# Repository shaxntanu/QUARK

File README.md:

<div align="center">

# QUARK

**A tiny desk display for Codex usage and live Windows telemetry.**

ESP32-C3 · 128×64 OLED · USB serial · Windows companion

</div>

QUARK pairs an ESP32-C3 SuperMini with a monochrome OLED. A lightweight Windows companion reads local PC metrics and Codex App Server usage, then sends them to the device over USB. A physical switch selects Codex or system pages; a button advances pages or requests a refresh.

## At a glance

- **Codex:** today's and lifetime tokens, seven-day token trend, five-hour and weekly allowance, usage streaks, and longest running turn.
- **PC:** CPU load and frequency, memory use and free memory, NVIDIA GPU load/temperature/VRAM, system-drive use/free space, network throughput, uptime, battery state when available, and a ChatGPT HTTPS reachability check.
- **OLED:** one clear metric or a pair of related readings per page, with line charts for changing values.
- **Connection:** USB reconnects automatically. A brief connection chime plays once after the selected feed is stable; temporary Codex errors keep the last readings visible until they age out.
- **Status LEDs:** blue for a healthy selected feed, red for offline/error, and red plus blue while connecting or refreshing. The faulty green channel is unused.

## Project status

The repository contains a Windows companion, ESP32-C3 firmware, KiCad source, and fabrication exports. The companion and firmware source identify themselves as version 1.2.0; the latest published GitHub release is `v1.1.0`. This audit rebuilt the software and checked the CAD files, but did not perform a new hardware-in-the-loop session.

The project is an engineering prototype and personal telemetry utility. It does not claim research novelty or measured performance results. No `LICENSE` file is present, so reuse and redistribution terms have not been specified.

## Engineering docs

- [Architecture and interfaces](docs/architecture.md)
- [Requirements and scope](docs/requirements.md)
- [Data collection methodology](docs/methodology.md)
- [Hardware integration](docs/hardware.md)
- [Verification evidence](docs/verification.md)
- [Traceability matrix](docs/traceability.md)
- [Security notes](docs/security.md)
- [Limitations](docs/limitations.md) and [roadmap proposals](docs/roadmap.md)
- [Compatibility matrix](docs/compatibility.md)
- [Failure analysis](docs/failure-analysis.md) and [assumptions](docs/assumptions.md)
- [Hardware references](docs/hardware-references.md)
- [Research sources](docs/research-sources.md)
- [Engineering evidence](docs/engineering-evidence.md)
- [Generated artifact provenance](docs/generated-artifacts.md)
- [AI change audit](docs/AI_CHANGE_AUDIT.md) and [skills registry](docs/AI_SKILLS_REFERENCE.md)
- [Decision records](docs/decisions/)
- [Dependency inventory](docs/sbom.md)
- [KiCad workflow research notes](docs/research-notes.md)
- [Repository audit summary](docs/audit.md)
- [Verification script](scripts/verify.ps1) and [documentation checker](scripts/check_docs.py)

The HTTPS indicator only checks whether the computer can open a TCP connection to `chatgpt.com` on port 443. It helps distinguish a general network problem from a Codex App Server problem; it does not prove that Codex authentication or usage requests are working.

## OLED pages

### Codex mode

1. Tokens today, with lifetime tokens in the footer.
2. Seven-day token trend, normalized to the busiest day in that period, with the peak count.
3. Five-hour allowance remaining and its reset estimate.
4. Weekly allowance remaining and its reset estimate.
5. Current and longest usage streak.
6. Longest running Codex turn.

### System mode

1. CPU load and current frequency.
2. Memory used and available memory.
3. GPU load and temperature.
4. GPU memory use.
5. System-drive use and free space.
6. Download and upload rates with separate trend charts.
7. ChatGPT HTTPS reachability, system uptime, and battery state when available.

NVIDIA GPU readings require `nvidia-smi`; they show `--` when that tool or a supported GPU is unavailable. CPU temperature is not reported because Windows' standard psutil interface does not provide it reliably.

## Hardware

The carrier PCB is designed for an **ESP32-C3 SuperMini 2×8** module and an SH1106 128×64 OLED.

| Part | ESP32-C3 GPIO |
|---|---:|
| OLED SDA | 0 |
| OLED SCL | 1 |
| Page/refresh button | 3 |
| Status LED red | 4 |
| Passive piezo buzzer | 5 |
| Codex/System switch | 6 |
| Status LED blue | 10 |

The button and switch use `INPUT_PULLUP` and should connect to GND when closed. Use current-limiting resistors for the red and blue LED channels. GPIO 7's faulty green channel is not used.

The KiCad schematic, PCB, BOM, previews, Gerbers, and drill files are in [`hardware/QUARK_SuperMini_Carrier`](hardware/QUARK_SuperMini_Carrier/README.md).

## Install the Windows companion

Build the standalone executable with Python 3.12:

```powershell
.\scripts\build_exe.ps1
```

Install it, add it to the current Windows user's Startup folder, and launch it:

```powershell
.\scripts\install_startup.ps1
```

The companion detects the QUARK serial device, reconnects after unplug/replug, and keeps PC telemetry running while Codex data is unavailable. Rotating diagnostic logs are stored in `%LOCALAPPDATA%\QUARK\quark.log`.

To remove the startup shortcut:

```powershell
.\scripts\remove_startup.ps1
```

Codex pages require the Codex CLI to be installed and signed in for the same Windows user. PC pages work independently. For diagnostics, run `py -3.12 .\quark.py --self-test`; list serial ports with `py -3.12 .\quark.py --list-ports`.

## Flash the firmware

1. Install the Arduino ESP32 core 3.x and the U8g2 library.
2. Open `QUARK.ino` in Arduino IDE and select an ESP32-C3 board.
3. Enable **USB CDC On Boot**.
4. Upload the sketch and close Serial Monitor before the companion connects.

The sketch uses `U8G2_SH1106_128X64_NONAME_F_HW_I2C`. Change the constructor if your OLED uses another controller. The companion does not flash the board.

## USB serial protocol

Messages are newline-terminated ASCII at 115200 baud. Values unavailable on the current computer are sent as `--`.

```text
AI|TODAY=18.4K|LIFE=1.42M|H5=74|WEEK=61|H5R=2h14m|WR=3d4h|PEAK=4.2K|STREAK=3|BEST=12|LONGEST=2h14m|D7=0,10,38,22,100,56,64
SYS|CPU=42|GPU=68|RAM=57|TEMP=71|VRAM=36|DISK=62|FREE=14.2G|DFREE=215G|DN=1.2M|UP=84K|DNP=24|UPP=3|FREQ=3.6G|SYSUP=3d4h|BAT=87|AC=ON|WEB=OK
```

The ESP32 answers `PING` with `PONG` for device discovery. It also accepts `MODE|AI`, `MODE|SYS`, `REFRESH|AI`, and `REFRESH|SYS`.

## Build firmware from the command line

With Arduino CLI and the required ESP32 core and U8g2 library installed:

```powershell
arduino-cli compile --fqbn esp32:esp32:esp32c3:CDCOnBoot=cdc .
```

## Development

Run the canonical Windows verification workflow with Python 3.12:

```powershell
py -3.12 -m pip install -r requirements.txt -r requirements-build.txt
.\scripts\verify.ps1
```

To include a local ESP32-C3 firmware compile, install Arduino CLI, the ESP32 core and U8g2, then run `.scriptserify.ps1 -IncludeFirmware`. KiCad ERC/DRC checks use the commands in the hardware README and are not part of the default script.

See [CONTRIBUTING.md](CONTRIBUTING.md) for the repeatable build and review workflow, and [SECURITY.md](SECURITY.md) for vulnerability reporting. Citations for version 1.2.0 are described in [CITATION.cff](CITATION.cff). The project has no declared license yet.

## Repository layout

```text
QUARK.ino                         ESP32-C3 firmware and OLED UI
quark.py                          Windows telemetry/Codex companion
tests/test_quark.py               Python unit and protocol regression tests
scripts/                          Windows packaging and startup scripts
hardware/QUARK_SuperMini_Carrier/ KiCad design, BOM, and fabrication files
docs/                             Architecture, verification, security, and audit docs
.github/                          CI and dependency update configuration
```

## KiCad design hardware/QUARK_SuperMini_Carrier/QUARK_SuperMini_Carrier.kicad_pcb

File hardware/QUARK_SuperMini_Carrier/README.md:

# QUARK ESP32-C3 SuperMini Carrier

KiCad source for a two-layer carrier board that connects QUARK's ESP32-C3 SuperMini, OLED, mode switch, page button, passive piezo, and red/blue status LEDs.

## Design files

- `QUARK_SuperMini_Carrier.kicad_pro`: KiCad project.
- `QUARK_SuperMini_Carrier.kicad_sch`: schematic.
- `QUARK_SuperMini_Carrier.kicad_pcb`: routed PCB.
- `QUARK.kicad_sym`, `QUARK.pretty/`, and the library tables: project-local symbol and footprint libraries.
- `BOM.csv`: board and off-board parts.
- `firmware/QUARK_ESP32-C3_SuperMini_CDC.bin`: merged 4 MB ESP32-C3 flash image with USB CDC on boot enabled.
- `fabrication/`: Gerbers, Excellon drill files, and drill maps.
- `preview/`: schematic and board preview images.
- `scripts/generate_schematic.py` and `scripts/generate_board.py`: source generators.

## Board and module fit

The carrier outline is 70.104 × 55.372 mm, 1.6 mm thick, with four 3.2 mm non-plated M3 holes. The module footprint is for an ESP32-C3 SuperMini with two 8-pin rows on 2.54 mm pitch and 15.24 mm between row centers. Fit two 1×8 female socket strips to the carrier, then plug the module in with its USB-C connector toward the board's top edge. The nominal module outline is 22.52 × 18 mm per the [module datasheet](https://dl.artronshop.co.th/ESP32-C3%20SuperMini%20datasheet.pdf); SuperMini clones vary, so compare the module and header spacing before ordering a batch.

## Connectors and assembly

All board connectors use 2.54 mm pitch. Connector pin 1 is identified on the silkscreen.

| Ref. | Pin order | Connection |
|---|---|---|
| J1 | GND, 3V3, SCL, SDA | External 128×64 OLED; SCL is GPIO1 and SDA is GPIO0. |
| J2 | AI, COM, SYS OPEN | SPDT mode switch: connect COM to AI/GND for AI mode; leave COM open for System mode (`INPUT_PULLUP`). |
| J3 | GPIO5, GND | Passive piezo disc only; plays startup/control tones and the new-connection acknowledgement. |
| SW1 | N/A | Page/refresh button from GPIO3 to GND. |
| D1, D2 | N/A | Red and blue active-high status LEDs, each with a 330 Ω series resistor. |

The OLED module and mode switch are off-board. J1–J3 are plated header footprints; install pin headers or solder leads as needed. Do not connect a high-current magnetic buzzer directly to GPIO5. The ESP32-C3 SuperMini provides the USB interface and board-level power regulation.

## Fabrication

The `fabrication/` folder contains copper, solder-mask, silkscreen, paste, and outline Gerbers, plus separate PTH and NPTH Excellon files and drill maps. Upload [`QUARK_SuperMini_Carrier_gerbers.zip`](fabrication/QUARK_SuperMini_Carrier_gerbers.zip) to the board fabricator, or upload the individual Gerber and drill files. The board uses two copper layers and a 1.6 mm FR-4 stackup.

## Validation

The checked-in design was checked with KiCad CLI 10.0.7. The 2026-11-02 reports contain zero included ERC/DRC violations, zero unconnected items, and zero schematic-parity issues. They also have 4 ERC checks and 7 DRC checks explicitly ignored; see [`docs/verification.md`](../../docs/verification.md) for the exact list. Zero included violations is not a complete manufacturing or assembly certification. Re-run checks after edits with KiCad 10:

```powershell
kicad-cli sch erc QUARK_SuperMini_Carrier.kicad_sch
kicad-cli pcb drc --schematic-parity --refill-zones QUARK_SuperMini_Carrier.kicad_pcb
```

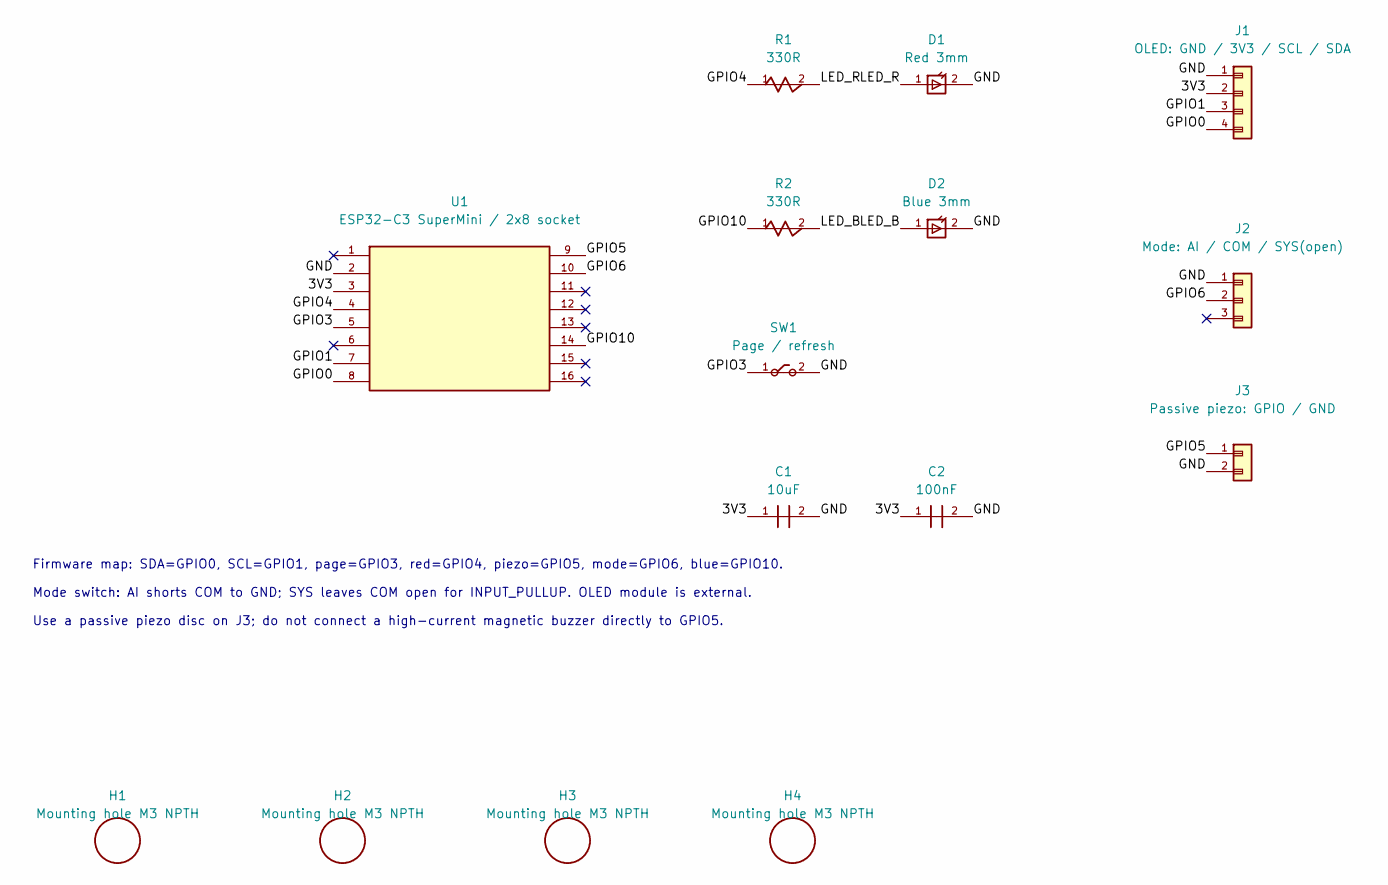
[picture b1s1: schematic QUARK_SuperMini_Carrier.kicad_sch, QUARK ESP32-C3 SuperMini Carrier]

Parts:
C1: 10uF; C_Disc_D5.0mm_W2.5mm_P5.00mm
C2: 100nF; C_Disc_D5.0mm_W2.5mm_P5.00mm
D1: Red 3mm; LED_D3.0mm
D2: Blue 3mm; LED_D3.0mm
H1, H2, H3, H4: Mounting hole M3 NPTH; MountingHole_3.2mm_M3
J1: OLED: GND / 3V3 / SCL / SDA; PinHeader_1x04_P2.54mm_Vertical
J2: Mode: AI / COM / SYS(open); PinHeader_1x03_P2.54mm_Vertical
J3: Passive piezo: GPIO / GND; PinHeader_1x02_P2.54mm_Vertical
R1, R2: 330R; R_Axial_DIN0204_L3.6mm_D1.6mm_P7.62mm_Horizontal
SW1: Page / refresh; SW_TH_Tactile_Omron_B3F-100x
U1: ESP32-C3 SuperMini / 2x8 socket; ESP32C3_SuperMini_Socket_2x8

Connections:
/3V3: C1.1, C2.1, J1.2, U1.3 (3V3)
/GND: C1.2, C2.2, D1.2 (K), D2.2 (K), J1.1, J2.1, J3.2, SW1.2, U1.2 (GND)
/GPIO0: J1.4, U1.8 (GPIO0)
/GPIO1: J1.3, U1.7 (GPIO1)
/GPIO3: SW1.1, U1.5 (GPIO3)
/GPIO4: R1.1, U1.4 (GPIO4)
/GPIO5: J3.1, U1.9 (GPIO5)
/GPIO6: J2.2, U1.10 (GPIO6)
/GPIO10: R2.1, U1.14 (GPIO10)
/LED_B: D2.1 (A), R2.2
/LED_R: D1.1 (A), R1.2

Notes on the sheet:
Firmware map: SDA=GPIO0, SCL=GPIO1, page=GPIO3, red=GPIO4, piezo=GPIO5, mode=GPIO6, blue=GPIO10.
Mode switch: AI shorts COM to GND; SYS leaves COM open for INPUT_PULLUP. OLED module is external.
Use a passive piezo disc on J3; do not connect a high-current magnetic buzzer directly to GPIO5.

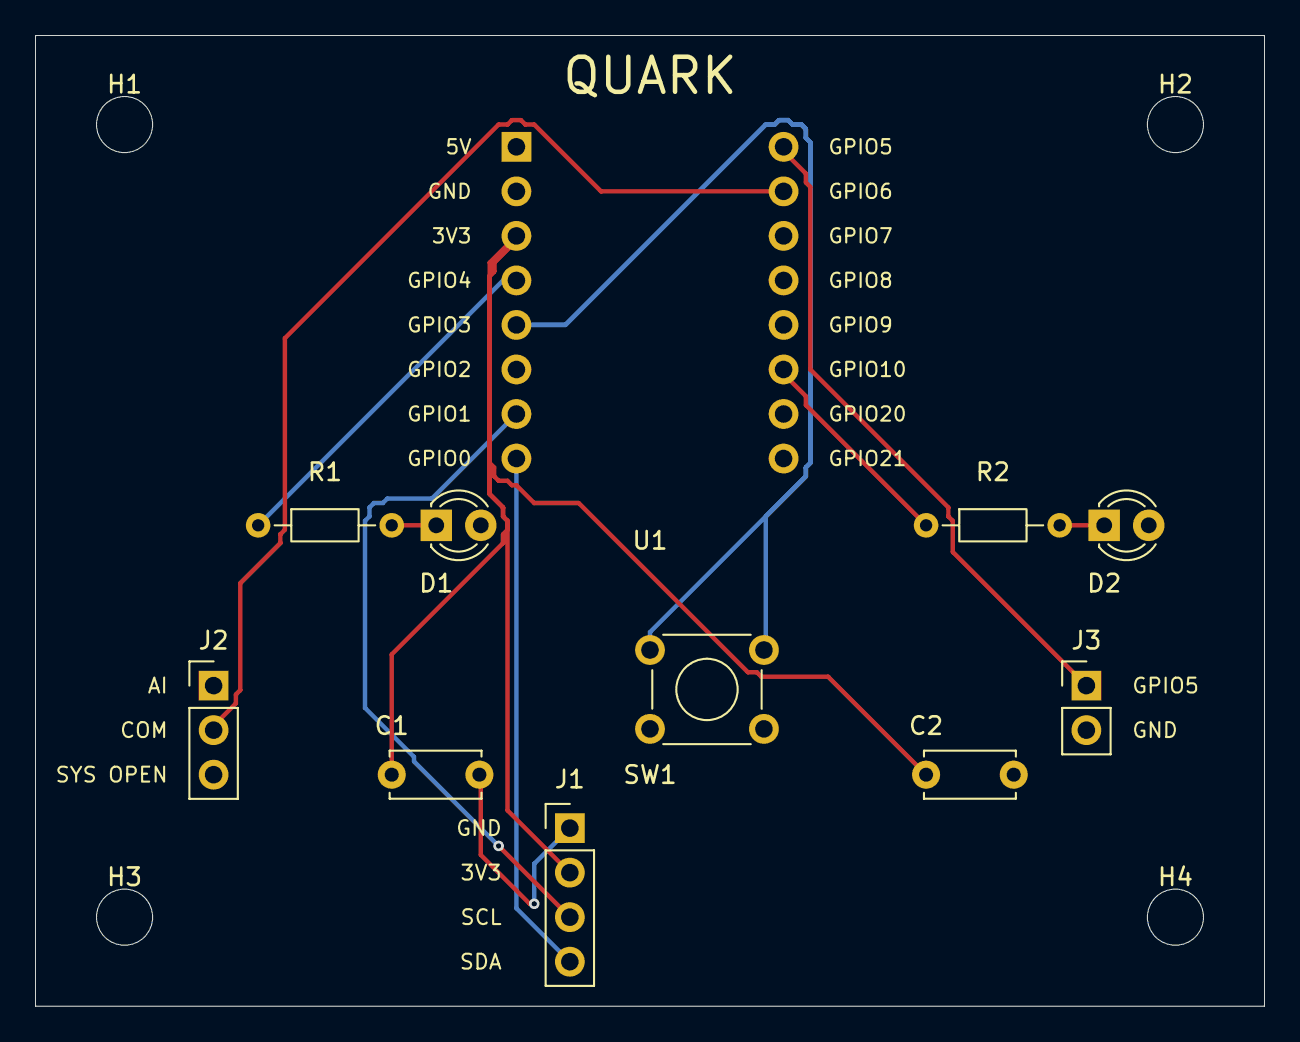
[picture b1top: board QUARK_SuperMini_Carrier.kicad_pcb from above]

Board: 2 copper layers, 70.1 x 55.4 mm, 15 parts (0 on the bottom side), 11 nets.

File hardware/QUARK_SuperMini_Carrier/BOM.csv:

Reference,Quantity,Description,Specification / footprint,Notes
U1,1,ESP32-C3 SuperMini module,2 x 8 pins; 2.54 mm pitch,USB-C faces board top; module not included with bare PCB
U1 socket,2,1 x 8 female socket strip,2.54 mm pitch,Install on carrier; socket rows are 15.24 mm center-to-center
J1,1,1 x 4 straight pin header or wire harness,2.54 mm pitch,External OLED: GND / 3V3 / SCL / SDA
J2,1,1 x 3 straight pin header or wire harness,2.54 mm pitch,External mode switch: AI / COM / SYS open
J3,1,1 x 2 straight pin header or wire harness,2.54 mm pitch,Passive piezo: GPIO5 / GND
R1 R2,2,Resistor,330 ohm; DIN0204 axial THT,LED current limiting
D1,1,Red through-hole LED,3 mm,Status LED
D2,1,Blue through-hole LED,3 mm,Status LED
SW1,1,Momentary tactile switch,Omron B3F-100x compatible footprint,Page / refresh button
C1,1,Ceramic capacitor,10 uF; 5 mm pitch THT,Power decoupling
C2,1,Ceramic capacitor,100 nF; 5 mm pitch THT,Power decoupling
OLED1,1,OLED module,128 x 64; SH1106; 4-wire I2C,Off-board accessory
SW2,1,SPDT mode switch,ON-ON; center common,Off-board accessory; COM to AI/GND or SYS/open
BZ1,1,Passive piezo disc,GPIO-compatible,Off-board accessory; do not use a high-current magnetic buzzer
H1-H4,4,M3 fastener set,3.2 mm clearance,Optional screws and standoffs for mounting
